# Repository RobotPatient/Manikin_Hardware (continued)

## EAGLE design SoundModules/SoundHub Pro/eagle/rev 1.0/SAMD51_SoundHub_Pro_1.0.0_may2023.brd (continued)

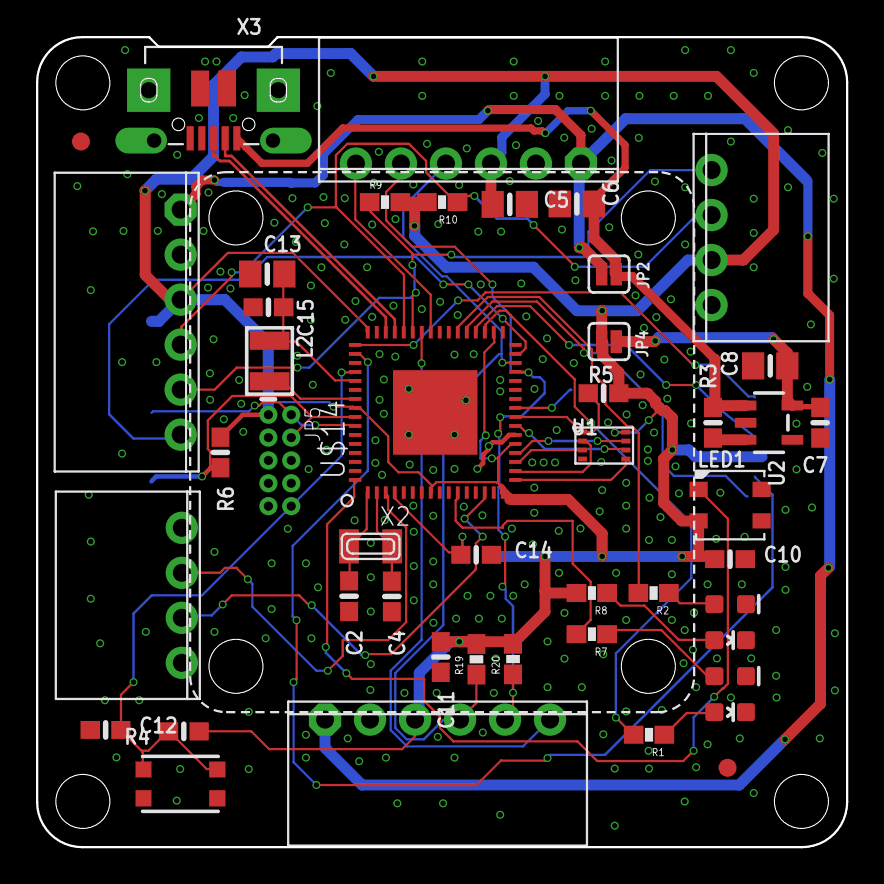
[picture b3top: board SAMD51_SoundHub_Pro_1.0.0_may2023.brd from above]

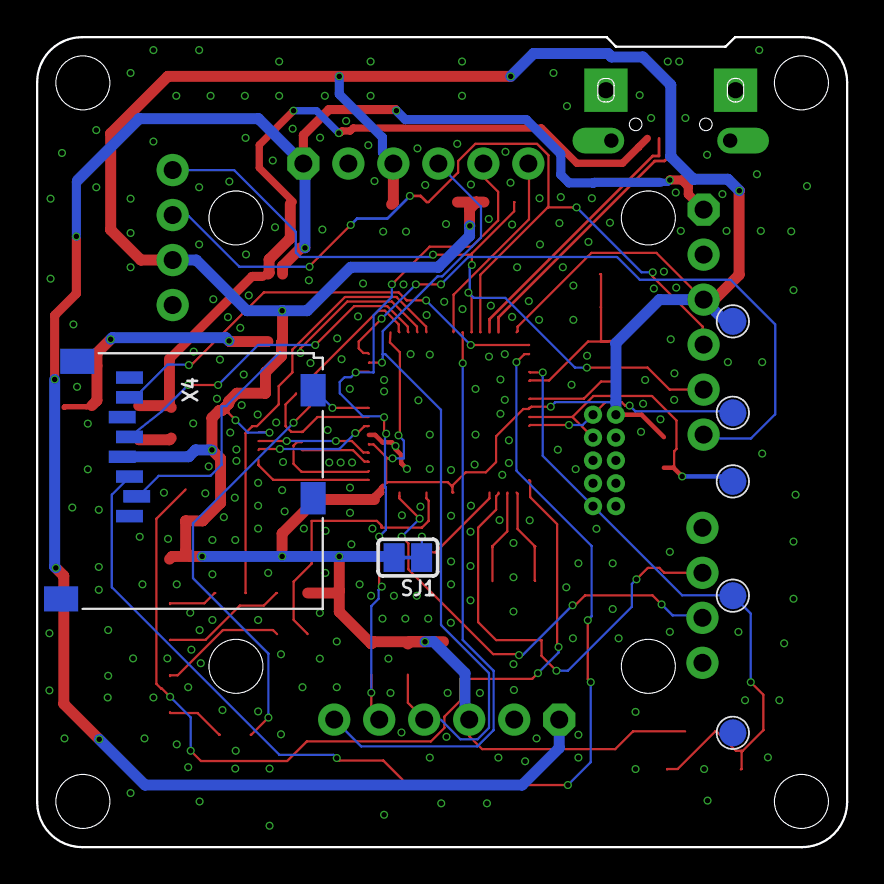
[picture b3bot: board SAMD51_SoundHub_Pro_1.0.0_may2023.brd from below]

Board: 2 copper layers, 45.0 x 45.0 mm, 51 parts (2 on the bottom side), 44 nets.

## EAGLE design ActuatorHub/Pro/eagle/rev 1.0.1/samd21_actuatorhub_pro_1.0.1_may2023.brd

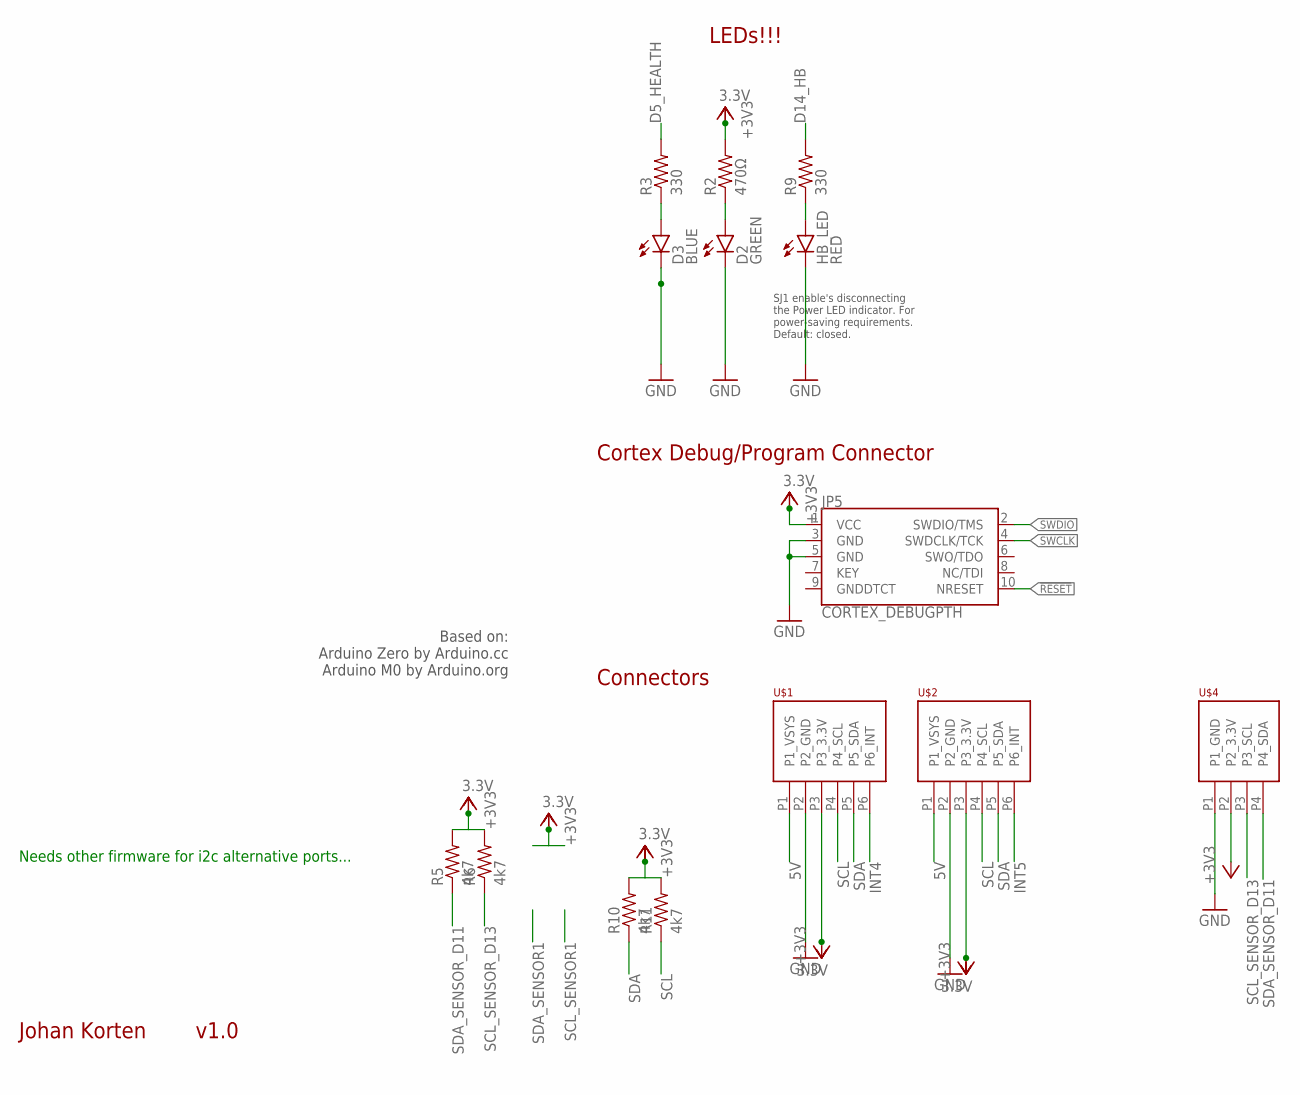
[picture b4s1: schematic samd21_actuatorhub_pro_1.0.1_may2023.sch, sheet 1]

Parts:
D2: GREEN; LED-0603
D3: BLUE; LED-0603
HB_LED: RED; LED-0603
JP5: CORTEX_DEBUGPTH; 2X5-PTH-1.27MM
R2: 470Ω; 0603-RES
R3, R9: 330; 0603-RES
R5, R6, R10, R11: 4k7; 0603-RES
U$1, U$2: PHOENIX_PTSM_M6_TH_I2CPPANGLE; PTSM_M6_THRHOLE
U$4: PHOENIX_PTSM_M4_THANGLE; PTSM_M4_TH

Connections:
3.3V: JP5.1 (VCC), R2.2, R5.2, R6.2, R10.2, R11.2, U$1.P3 (P3_3.3V), U$2.P3 (P3_3.3V), U$4.P2 (P2_3.3V); also elsewhere on the board
5V: U$1.P1 (P1_VSYS), U$2.P1 (P1_VSYS); also elsewhere on the board
!RESET: JP5.10 (NRESET); also elsewhere on the board
D5_HEALTH: R3.2; also elsewhere on the board
D5_HEALTH_LED: D3.A, R3.1
D14_HB: R9.2; also elsewhere on the board
D14_HB_LED: HB_LED.A, R9.1
GND: D2.C, D3.C, HB_LED.C, JP5.3 (GND), JP5.5 (GND), U$1.P2 (P2_GND), U$2.P2 (P2_GND), U$4.P1 (P1_GND); also elsewhere on the board
INT4: U$1.P6 (P6_INT); also elsewhere on the board
INT5: U$2.P6 (P6_INT); also elsewhere on the board
unnamed: D2.A, R2.1
SCL: R11.1, U$1.P4 (P4_SCL), U$2.P4 (P4_SCL); also elsewhere on the board
SCL_SENSOR_D13: R6.1, U$4.P3 (P3_SCL); also elsewhere on the board
SDA: R10.1, U$1.P5 (P5_SDA), U$2.P5 (P5_SDA); also elsewhere on the board
SDA_SENSOR_D11: R5.1, U$4.P4 (P4_SDA); also elsewhere on the board
SWCLK: JP5.4 (SWDCLK/TCK); also elsewhere on the board
SWDIO: JP5.2 (SWDIO/TMS); also elsewhere on the board

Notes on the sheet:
LEDs!!!
Cortex Debug/Program Connector
Connectors
Johan Korten
v1.0
SJ1 enable's disconnecting the Power LED indicator. For power-saving requirements. Default: closed.
Based on: Arduino Zero by Arduino.cc Arduino M0 by Arduino.org
Needs other firmware for i2c alternative ports...

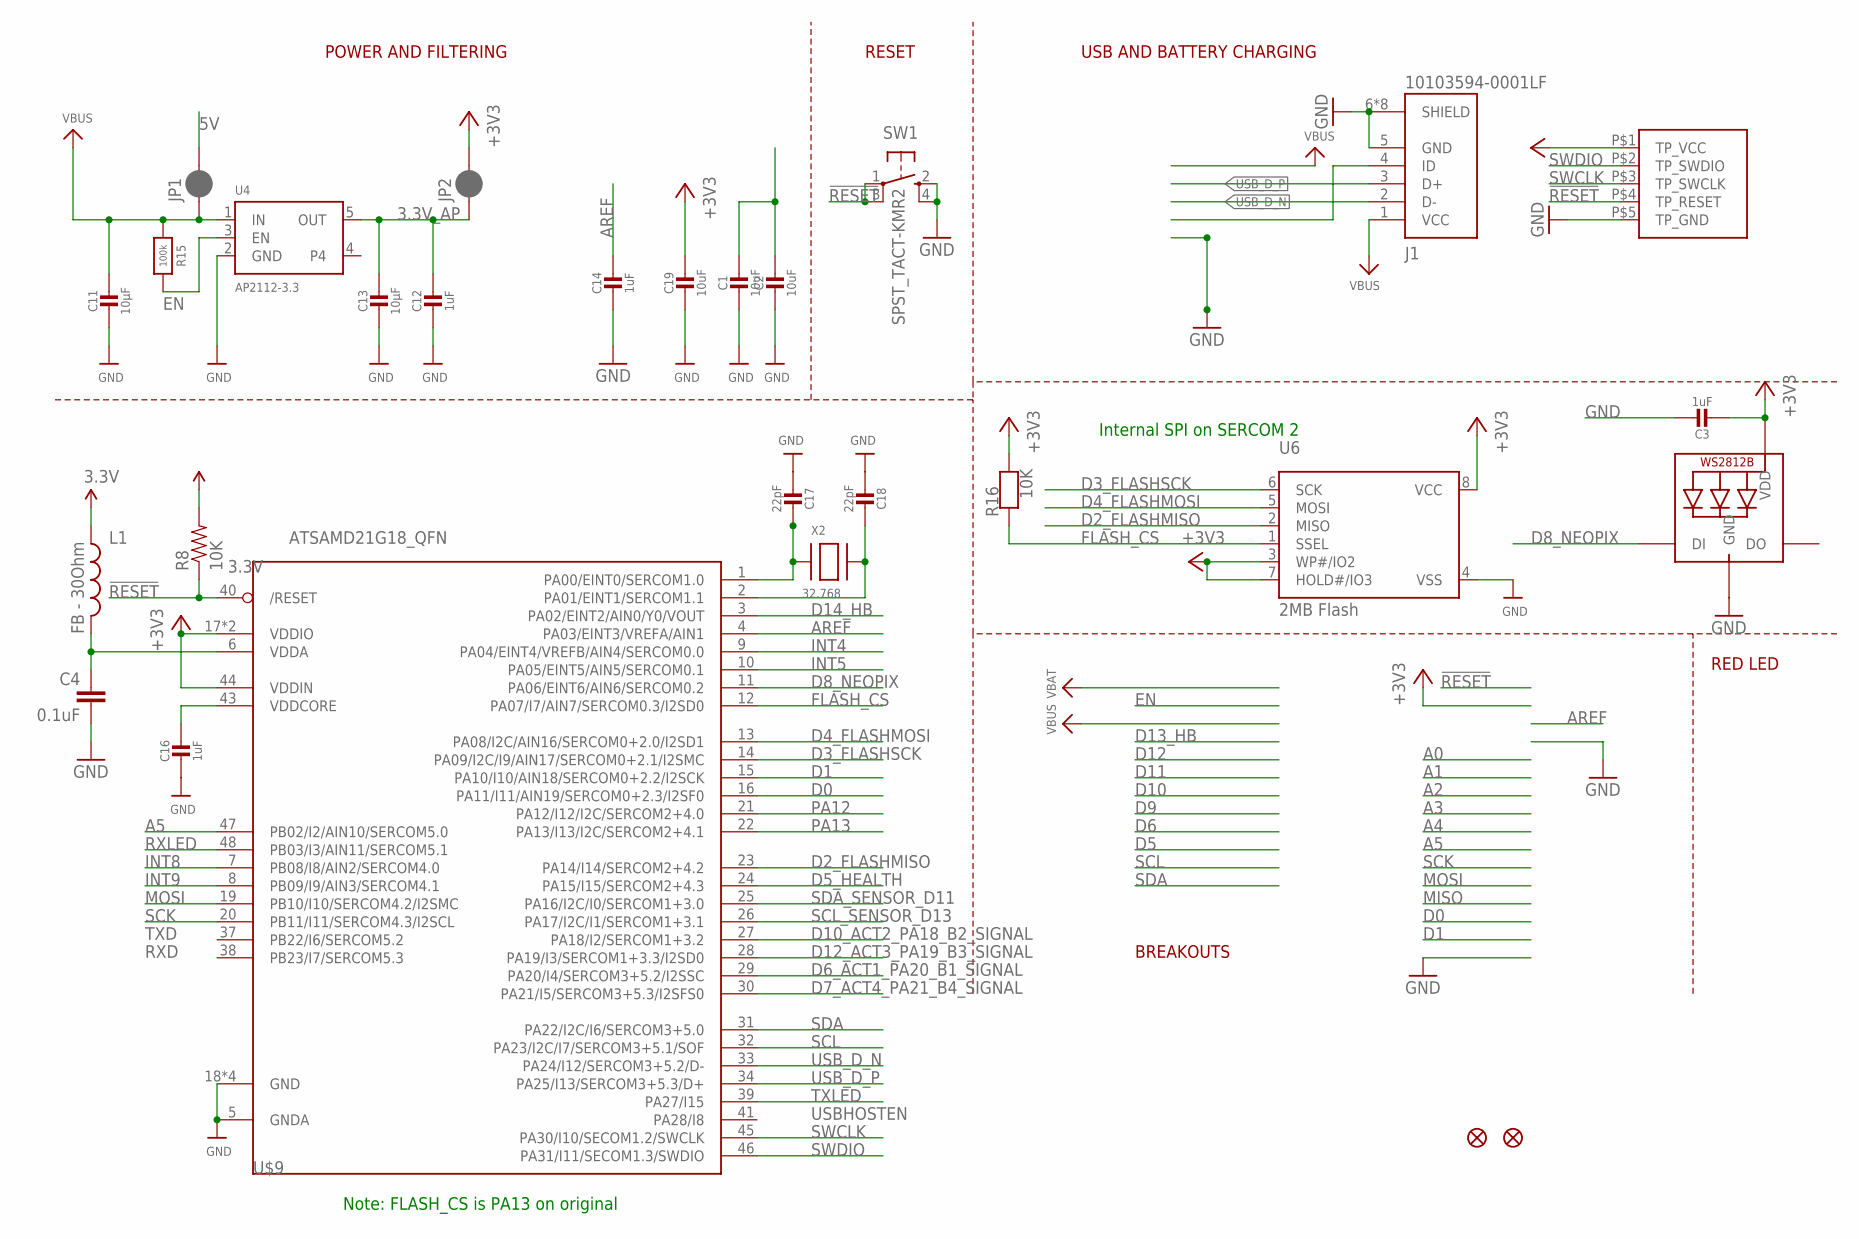
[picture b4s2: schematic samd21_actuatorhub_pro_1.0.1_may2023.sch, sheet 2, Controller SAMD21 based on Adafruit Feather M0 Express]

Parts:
C1, C2, C19: 10uF; 0805-NO
C3, C12, C14, C16: 1uF; 0603-NO
C4: 0.1uF; 0402-CAP
C11, C13: 10µF; 0805-NO
C17, C18: 22pF; 0603-NO
J1: 10103594-0001LF; AMPHENOL_10103594-0001LF
JP1, JP2: JUMPER-SMT_2_NC_PASTE_SILK; SMT-JUMPER_2_NC_PASTE_SILK
L1: FB - 30Ohm; 0603
LED1: WS2812B3535; LED3535
R8: 10K; 0603-RES
R15: 100k; 0603-NO
R16: 10K; 0603-NO
SW1: SPST_TACT-KMR2; KMR2
U4: AP2112-3.3; SOT23-5
U6: 2MB Flash; SOIC8_208MIL
U$5: HUB_TESTPINSHUBS; TEST_PINS
U$9: ATSAMD21G18_QFN; TQFN48_7MM
U$34, U$35: FIDUCIAL""; FIDUCIAL_1MM
X2: 32.768; XTAL3215

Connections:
3.3V: C3.2, C19.1, JP2.2, L1.1, LED1.2 (VDD), R8.2, R16.2, U6.3 (WP#/IO2), U6.7 (HOLD#/IO3), U6.8 (VCC), U$5.P$1 (TP_VCC), U$9.17 (VDDIO), U$9.36 (VDDIO), U$9.44 (VDDIN); also elsewhere on the board
3.3V_AP: C12.1, C13.1, JP2.1, U4.5 (OUT)
5V: C1.1, C2.1, JP1.2; also elsewhere on the board
!RESET: R8.1, SW1.1, SW1.3 (P1), U$5.P$4 (TP_RESET), U$9.40 (/RESET); also elsewhere on the board
A5: U$9.47 (PB02/I2/AIN10/SERCOM5.0)
AREF: C14.1, U$9.4 (PA03/EINT3/VREFA/AIN1)
D0: U$9.16 (PA11/I11/AIN19/SERCOM0+2.3/I2SF0)
D1: U$9.15 (PA10/I10/AIN18/SERCOM0+2.2/I2SCK)
D2_FLASHMISO: U6.2 (MISO), U$9.23 (PA14/I14/SERCOM2+4.2)
D3_FLASHSCK: U6.6 (SCK), U$9.14 (PA09/I2C/I9/AIN17/SERCOM0+2.1/I2SMC)
D4_FLASHMOSI: U6.5 (MOSI), U$9.13 (PA08/I2C/AIN16/SERCOM0+2.0/I2SD1)
D5_HEALTH: U$9.24 (PA15/I15/SERCOM2+4.3); also elsewhere on the board
D6_ACT1_PA20_B1_SIGNAL: U$9.29 (PA20/I4/SERCOM3+5.2/I2SSC); also elsewhere on the board
D7_ACT4_PA21_B4_SIGNAL: U$9.30 (PA21/I5/SERCOM3+5.3/I2SFS0); also elsewhere on the board
D8_NEOPIX: LED1.1 (DI), U$9.11 (PA06/EINT6/AIN6/SERCOM0.2)
D10_ACT2_PA18_B2_SIGNAL: U$9.27 (PA18/I2/SERCOM1+3.2); also elsewhere on the board
D12_ACT3_PA19_B3_SIGNAL: U$9.28 (PA19/I3/SERCOM1+3.3/I2SD0); also elsewhere on the board
D14_HB: U$9.3 (PA02/EINT2/AIN0/Y0/VOUT); also elsewhere on the board
EN: R15.2, U4.3 (EN)
FLASH_CS: R16.1, U6.1 (SSEL), U$9.12 (PA07/I7/AIN7/SERCOM0.3/I2SD0)
GND: C1.2, C2.2, C3.1, C4.2, C11.2, C12.2, C13.2, C14.2, C16.2, C17.2, C18.2, C19.2, J1.5 (GND), J1.6 (SHIELD), J1.7 (SHIELD), J1.8 (SHIELD), J1.9 (SHIELD), J1.10 (SHIELD), J1.11 (SHIELD), J1.S1 (SHIELD), J1.S2 (SHIELD), LED1.4 (GND), SW1.2 (S), SW1.4 (S1), U4.2 (GND), U6.4 (VSS), U$5.P$5 (TP_GND), U$9.5 (GNDA), U$9.18 (GND), U$9.35 (GND), U$9.42 (GND), U$9.THERMAL (GND); also elsewhere on the board
INT4: U$9.9 (PA04/EINT4/VREFB/AIN4/SERCOM0.0); also elsewhere on the board
INT5: U$9.10 (PA05/EINT5/AIN5/SERCOM0.1); also elsewhere on the board
INT8: U$9.7 (PB08/I8/AIN2/SERCOM4.0)
INT9: U$9.8 (PB09/I9/AIN3/SERCOM4.1)
MOSI: U$9.19 (PB10/I10/SERCOM4.2/I2SMC)
unnamed: C17.1, U$9.1 (PA00/EINT0/SERCOM1.0), X2.P$1
unnamed: C18.1, U$9.2 (PA01/EINT1/SERCOM1.1), X2.P$2
PA12: U$9.21 (PA12/I12/I2C/SERCOM2+4.0)
PA13: U$9.22 (PA13/I13/I2C/SERCOM2+4.1)
RXLED: U$9.48 (PB03/I3/AIN11/SERCOM5.1)
SCK: U$9.20 (PB11/I11/SERCOM4.3/I2SCL)
SCL: U$9.32 (PA23/I2C/I7/SERCOM3+5.1/SOF); also elsewhere on the board
SCL_SENSOR_D13: U$9.26 (PA17/I2C/I1/SERCOM1+3.1); also elsewhere on the board
SDA: U$9.31 (PA22/I2C/I6/SERCOM3+5.0); also elsewhere on the board
SDA_SENSOR_D11: U$9.25 (PA16/I2C/I0/SERCOM1+3.0); also elsewhere on the board
SWCLK: U$5.P$3 (TP_SWCLK), U$9.45 (PA30/I10/SECOM1.2/SWCLK); also elsewhere on the board
SWDIO: U$5.P$2 (TP_SWDIO), U$9.46 (PA31/I11/SECOM1.3/SWDIO); also elsewhere on the board
TXLED: U$9.39 (PA27/I15)
USB_D_N: J1.2 (D-), U$9.33 (PA24/I12/SERCOM3+5.2/D-)
USB_D_P: J1.3 (D+), U$9.34 (PA25/I13/SERCOM3+5.3/D+)
VBUS: C11.1, J1.1 (VCC), JP1.1, R15.1, U4.1 (IN)
VDDANA: C4.1, L1.2, U$9.6 (VDDA)
VDDCORE1: C16.1, U$9.43 (VDDCORE)

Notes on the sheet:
POWER AND FILTERING
RESET
USBHOSTEN
TXD
RXD
USB AND BATTERY CHARGING
BREAKOUTS
RED LED
Internal SPI on SERCOM 2
Note: FLASH_CS is PA13 on original

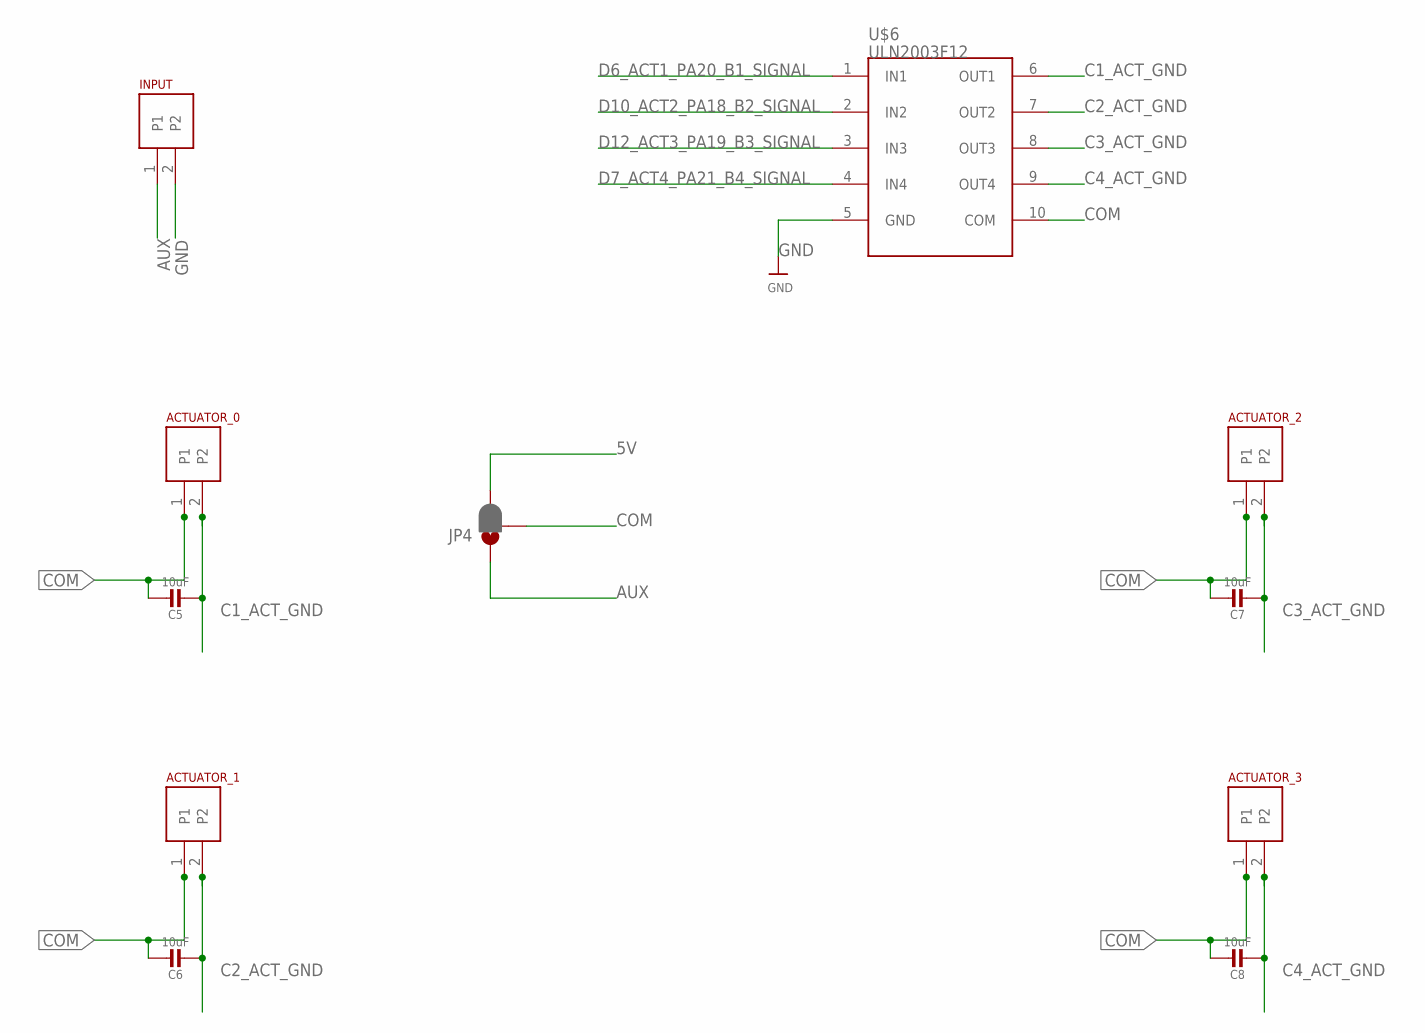
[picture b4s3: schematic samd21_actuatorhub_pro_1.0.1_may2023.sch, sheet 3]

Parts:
ACTUATOR_0, ACTUATOR_1: PHOENIX_PTSM_M2_TH; PTSM_M2_THRHOLE
ACTUATOR_2, ACTUATOR_3: PHOENIX_PTSM_M2TH; PTSM_M2_THRHOLE
C5, C6, C7, C8: 10uF; 0805-NO
INPUT: PHOENIX_PTSM_M2_TH; PTSM_M2_THRHOLE
JP4: JUMPER-SMT_3_1-NC_PASTE_SILK; SMT-JUMPER_3_1-NC_PASTE_SILK
U$6: ULN2003F12; U-DFN3030-10

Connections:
5V: JP4.3; also elsewhere on the board
AUX: INPUT.1, JP4.1
C1_ACT_GND: ACTUATOR_0.2, C5.2, U$6.6 (OUT1)
C2_ACT_GND: ACTUATOR_1.2, C6.2, U$6.7 (OUT2)
C3_ACT_GND: ACTUATOR_2.2, C7.2, U$6.8 (OUT3)
C4_ACT_GND: ACTUATOR_3.2, C8.2, U$6.9 (OUT4)
COM: ACTUATOR_0.1, ACTUATOR_1.1, ACTUATOR_2.1, ACTUATOR_3.1, C5.1, C6.1, C7.1, C8.1, JP4.2, U$6.10 (COM)
D6_ACT1_PA20_B1_SIGNAL: U$6.1 (IN1); also elsewhere on the board
D7_ACT4_PA21_B4_SIGNAL: U$6.4 (IN4); also elsewhere on the board
D10_ACT2_PA18_B2_SIGNAL: U$6.2 (IN2); also elsewhere on the board
D12_ACT3_PA19_B3_SIGNAL: U$6.3 (IN3); also elsewhere on the board
GND: INPUT.2, U$6.5 (GND); also elsewhere on the board

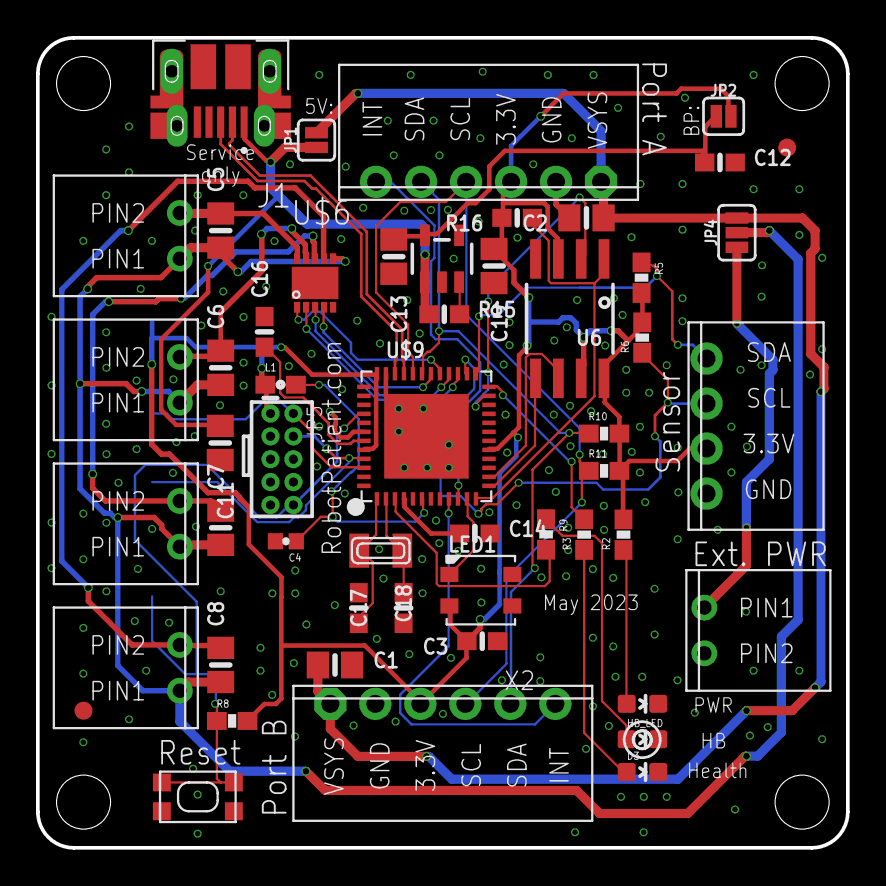
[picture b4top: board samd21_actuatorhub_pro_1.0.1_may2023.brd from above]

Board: 2 copper layers, 45.0 x 45.0 mm, 53 parts (0 on the bottom side), 42 nets.

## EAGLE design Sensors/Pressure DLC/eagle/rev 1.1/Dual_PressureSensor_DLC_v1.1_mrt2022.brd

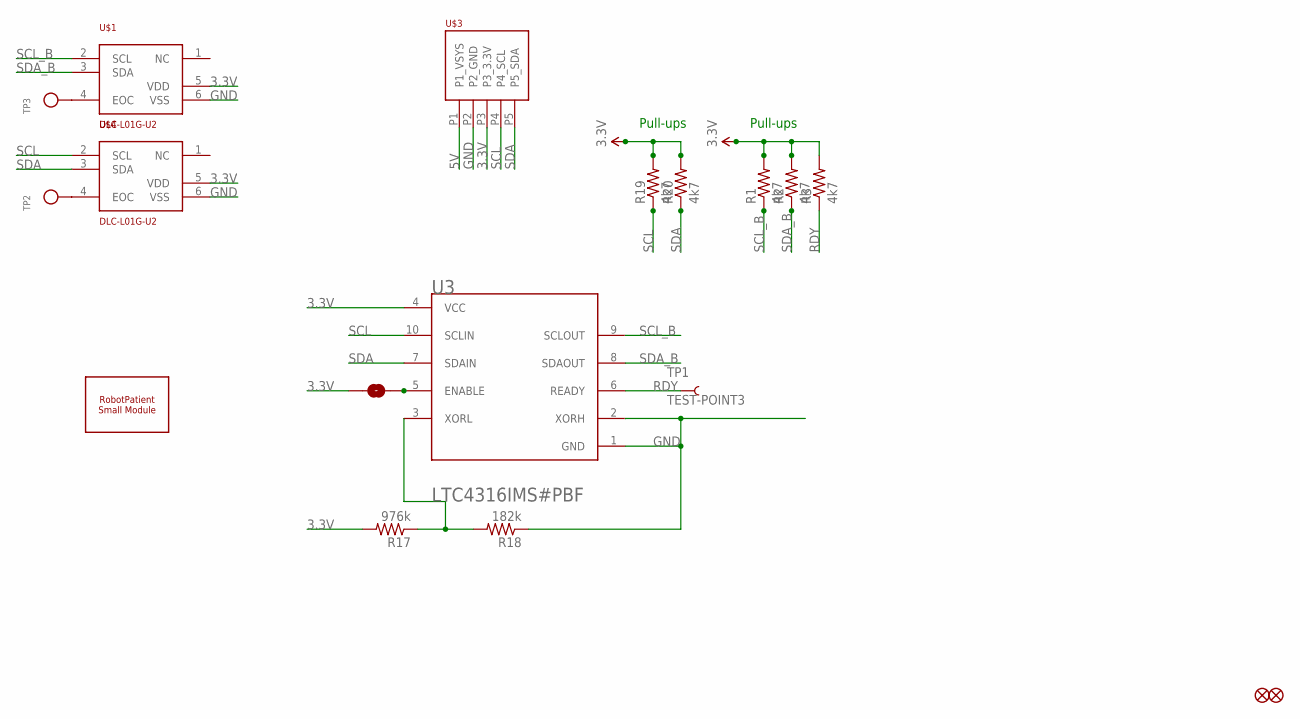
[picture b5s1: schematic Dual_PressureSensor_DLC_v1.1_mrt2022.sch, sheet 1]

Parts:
FID1, FID2: FIDUCIAL""; FIDUCIAL_1MM
JP3: JUMPER-SMT_2_NO_NO-SILK; SMT-JUMPER_2_NO_NO-SILK
R1, R2, R3, R19, R20: 4k7; 0603-RES
R17: 976k; 0603-RES
R18: 182k; 0603-RES
TP1: TEST-POINT3; PAD.03X.03
TP2, TP3: TESTPOINTROUND1MM; TESTPOINT_ROUND_1MM
U3: ANALOG_DEVICES_LTC4316IMS#PBFANALOG_DEVICES_LTC43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; ANALOG_DEVICES_LTC4316IMS#PBF_0
U$1, U$4: DLC-L01G-U2
U$2: ROBOTPATIENT_SMALL_MODULEBOARD; RP_SMALL_SENSOR_OUTLINE
U$3: PHOENIX_PTSM_M5_TH_I2C++; PTSM_M5_THRHOLE

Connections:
3.3V: JP3.1, R1.2, R2.2, R3.2, R17.2, R19.2, R20.2, U3.4 (VCC), U$1.5 (VDD), U$3.P3 (P3_3.3V), U$4.5 (VDD); also elsewhere on the board
5V: U$3.P1 (P1_VSYS); also elsewhere on the board
GND: R18.1, U3.1 (GND), U3.2 (XORH), U$1.6 (VSS), U$3.P2 (P2_GND), U$4.6 (VSS); also elsewhere on the board
unnamed: TP2.P$1, U$4.4 (EOC)
unnamed: TP3.P$1, U$1.4 (EOC)
unnamed: JP3.2, U3.5 (ENABLE)
unnamed: R17.1, R18.2, U3.3 (XORL)
RDY: R3.1, TP1.P$1, U3.6 (READY)
SCL: R19.1, U3.10 (SCLIN), U$3.P4 (P4_SCL), U$4.2 (SCL)
SCL_B: R1.1, U3.9 (SCLOUT), U$1.2 (SCL)
SDA: R20.1, U3.7 (SDAIN), U$3.P5 (P5_SDA), U$4.3 (SDA)
SDA_B: R2.1, U3.8 (SDAOUT), U$1.3 (SDA)

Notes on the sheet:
Pull-ups

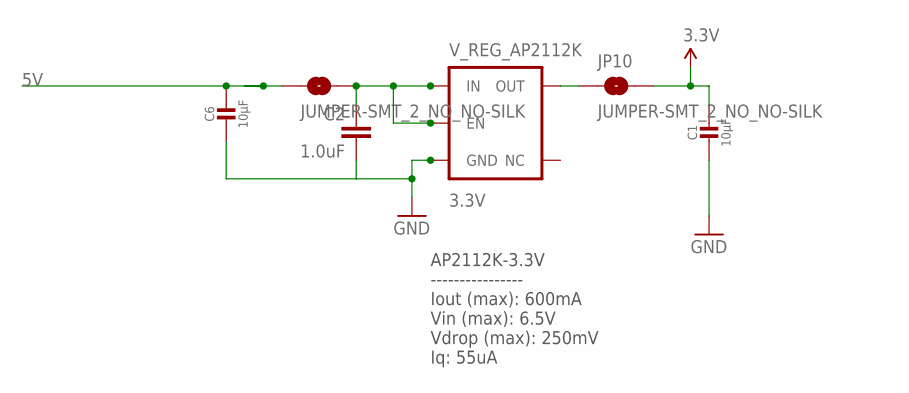
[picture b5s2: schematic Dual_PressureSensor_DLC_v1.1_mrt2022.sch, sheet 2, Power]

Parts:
C1, C6: 10µF; 0805-NO
C2: 1.0uF; 0805-CAP
JP10, JP11: JUMPER-SMT_2_NO_NO-SILK; SMT-JUMPER_2_NO_NO-SILK
V_REG_AP2112K: 3.3V; SOT23-5

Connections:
3.3V: C1.1, JP10.2; also elsewhere on the board
5V: C6.1, JP11.1; also elsewhere on the board
GND: C1.2, C2.2, C6.2, V_REG_AP2112K.2 (GND); also elsewhere on the board
unnamed: JP10.1, V_REG_AP2112K.5 (OUT)
unnamed: C2.1, JP11.2, V_REG_AP2112K.1 (IN), V_REG_AP2112K.3 (EN)

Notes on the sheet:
AP2112K-3.3V ---------------- Iout (max): 600mA Vin (max): 6.5V Vdrop (max): 250mV Iq: 55uA

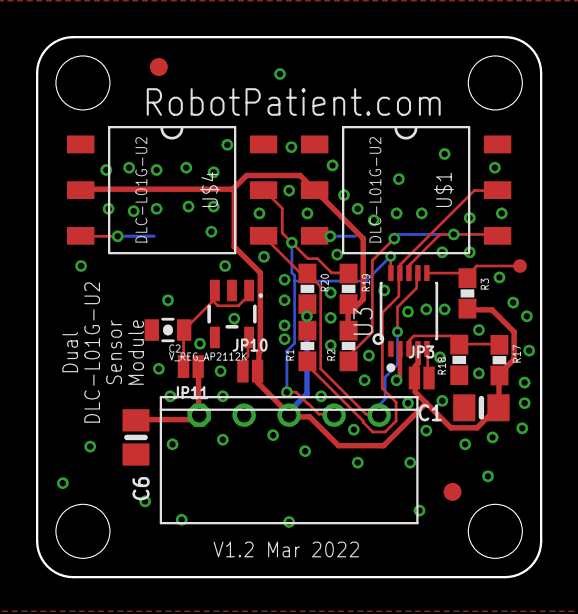
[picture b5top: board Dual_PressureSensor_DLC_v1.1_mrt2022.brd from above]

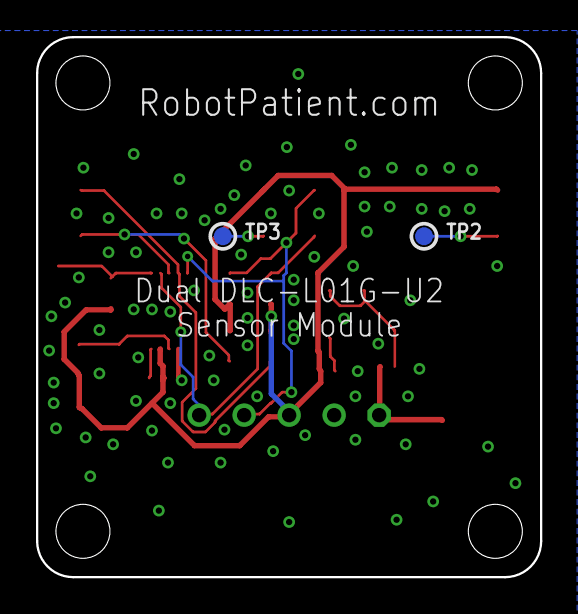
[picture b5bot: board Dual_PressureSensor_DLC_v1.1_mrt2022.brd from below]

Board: 2 copper layers, 28.0 x 30.0 mm, 24 parts (2 on the bottom side), 14 nets.

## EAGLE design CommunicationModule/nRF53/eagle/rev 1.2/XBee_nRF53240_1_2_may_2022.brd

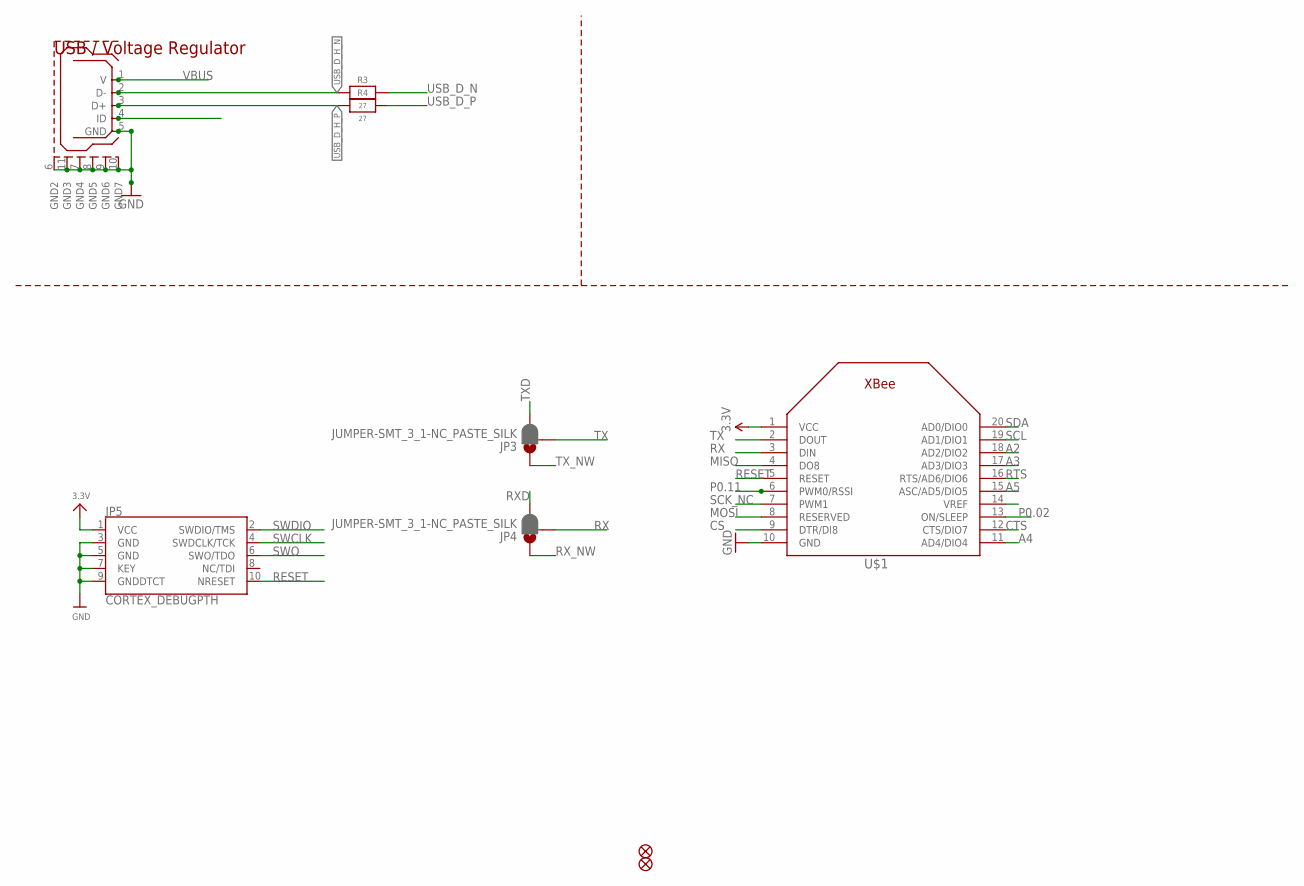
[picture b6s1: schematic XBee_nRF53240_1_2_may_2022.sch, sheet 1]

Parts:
FID1, FID3: FIDUCIAL_1MM
JP3, JP4: JUMPER-SMT_3_1-NC_PASTE_SILK; SMT-JUMPER_3_1-NC_PASTE_SILK
JP5: CORTEX_DEBUGPTH; 2X5-PTH-1.27MM
R3, R4: 27; 0603-NO
U$1: XBEE
U$2: USB_MICROB; USB_MICROB_PACKAGE

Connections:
3.3V: JP5.1 (VCC), U$1.1 (VCC); also elsewhere on the board
A2: U$1.18 (AD2/DIO2)
A3: U$1.17 (AD3/DIO3)
A4: U$1.11 (AD4/DIO4)
A5: U$1.15 (ASC/AD5/DIO5)
CS: U$1.9 (DTR/DI8)
CTS: U$1.12 (CTS/DIO7); also elsewhere on the board
GND: JP5.3 (GND), JP5.5 (GND), JP5.7 (KEY), JP5.9 (GNDDTCT), U$1.10 (GND), U$2.5 (GND), U$2.6 (GND2), U$2.7 (GND4), U$2.8 (GND5), U$2.9 (GND6), U$2.10 (GND7), U$2.11 (GND3); also elsewhere on the board
MISO: U$1.4 (DO8)
MOSI: U$1.8 (RESERVED)
P0.02: U$1.13 (ON/SLEEP)
P0.11: U$1.6 (PWM0/RSSI)
RESET: JP5.10 (NRESET), U$1.5 (RESET); also elsewhere on the board
RTS: U$1.16 (RTS/AD6/DIO6); also elsewhere on the board
RX: JP4.2, U$1.3 (DIN)
RXD: JP4.3; also elsewhere on the board
RX_NW: JP4.1; also elsewhere on the board
SCK_NC: U$1.7 (PWM1)
SCL: U$1.19 (AD1/DIO1); also elsewhere on the board
SDA: U$1.20 (AD0/DIO0); also elsewhere on the board
SWCLK: JP5.4 (SWDCLK/TCK); also elsewhere on the board
SWDIO: JP5.2 (SWDIO/TMS); also elsewhere on the board
SWO: JP5.6 (SWO/TDO)
TX: JP3.2, U$1.2 (DOUT)
TXD: JP3.3; also elsewhere on the board
TX_NW: JP3.1; also elsewhere on the board
USB_D_H_N: R3.1, U$2.2 (D-)
USB_D_H_P: R4.1, U$2.3 (D+)
USB_D_N: R3.2; also elsewhere on the board
USB_D_P: R4.2; also elsewhere on the board
VBUS: U$2.1 (V); also elsewhere on the board

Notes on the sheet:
USB / Voltage Regulator

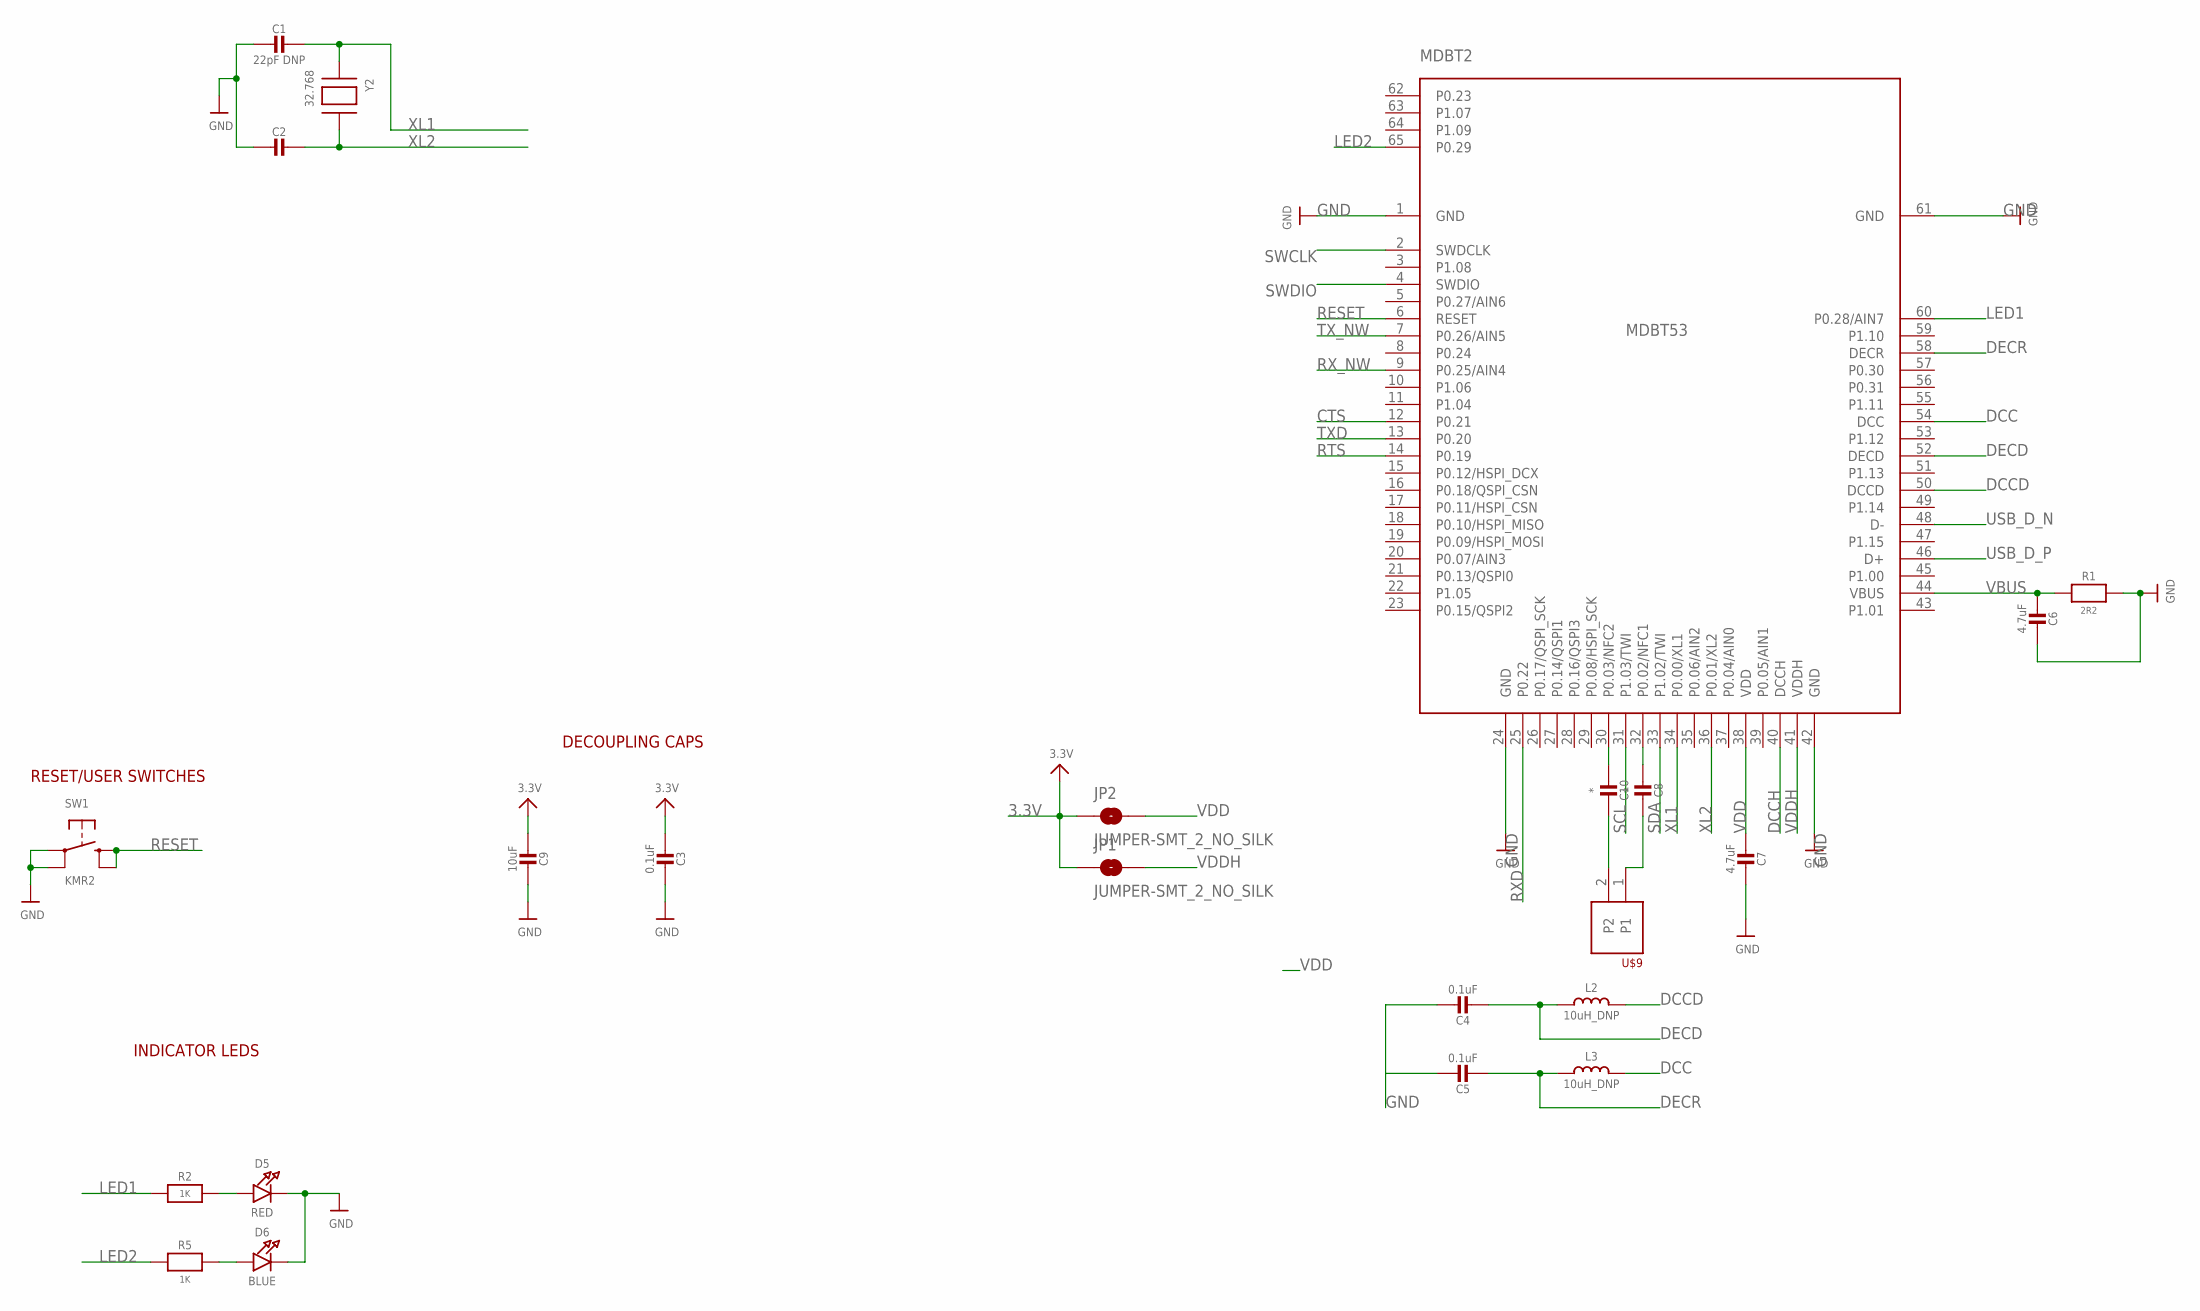
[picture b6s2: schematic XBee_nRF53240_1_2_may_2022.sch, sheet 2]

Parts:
C1, C2: 22pF DNP; 0603-NO
C3, C4, C5: 0.1uF; 0603-NO
C6, C7: 4.7uF; 0805-NO
C8, C10: *; 0603-NO
C9: 10uF; 0805-NO
D5: RED; CHIPLED_0805_NOOUTLINE
D6: BLUE; CHIPLED_0805_NOOUTLINE
JP1, JP2: JUMPER-SMT_2_NO_SILK; SMT-JUMPER_2_NO_SILK
L2, L3: 10uH_DNP; _0805MP
MDBT2: MDBT53
R1: 2R2; 0603-NO
R2, R5: 1K; 0603-NO
SW1: KMR2; BTN_KMR2_4.6X2.8
U$9: PHOENIX_PTSM_M2_TH; PTSM_M2_THRHOLE
Y2: 32.768; XTAL3215

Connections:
3.3V: C3.2, C9.2, JP1.1, JP2.1; also elsewhere on the board
CTS: MDBT2.12 (P0.21); also elsewhere on the board
DCC: L3.2, MDBT2.54 (DCC)
DCCD: L2.2, MDBT2.50 (DCCD)
DCCH: MDBT2.40 (DCCH)
DECD: C4.2, L2.1, MDBT2.52 (DECD)
DECR: C5.2, L3.1, MDBT2.58 (DECR)
GND: C1.2, C2.2, C3.1, C4.1, C6.1, C7.1, C9.1, D5.C, D6.C, MDBT2.1 (GND), MDBT2.24 (GND), MDBT2.42 (GND), MDBT2.61 (GND), R1.2, SW1.A, SW1.A' (P1); also elsewhere on the board
LED1: MDBT2.60 (P0.28/AIN7), R2.1
LED2: MDBT2.65 (P0.29), R5.1
unnamed: C10.2, MDBT2.30 (P0.03/NFC2)
unnamed: C8.2, MDBT2.32 (P0.02/NFC1)
unnamed: C10.1, U$9.2
unnamed: C8.1, U$9.1
unnamed: D6.A, R5.2
unnamed: D5.A, R2.2
RESET: MDBT2.6 (RESET), SW1.B (S), SW1.B' (S1); also elsewhere on the board
RTS: MDBT2.14 (P0.19); also elsewhere on the board
RXD: MDBT2.25 (P0.22); also elsewhere on the board
RX_NW: MDBT2.9 (P0.25/AIN4); also elsewhere on the board
SCL: MDBT2.31 (P1.03/TWI); also elsewhere on the board
SDA: MDBT2.33 (P1.02/TWI); also elsewhere on the board
SWCLK: MDBT2.2 (SWDCLK); also elsewhere on the board
SWDIO: MDBT2.4 (SWDIO); also elsewhere on the board
TXD: MDBT2.13 (P0.20); also elsewhere on the board
TX_NW: MDBT2.7 (P0.26/AIN5); also elsewhere on the board
USB_D_N: MDBT2.48 (D-); also elsewhere on the board
USB_D_P: MDBT2.46 (D+); also elsewhere on the board
VBUS: C6.2, MDBT2.44 (VBUS), R1.1; also elsewhere on the board
VDD: C7.2, JP2.2, MDBT2.38 (VDD)
VDDH: JP1.2, MDBT2.41 (VDDH)
XL1: C1.1, MDBT2.34 (P0.00/XL1), Y2.P$1
XL2: C2.1, MDBT2.36 (P0.01/XL2), Y2.P$2

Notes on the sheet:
INDICATOR LEDS
RESET/USER SWITCHES
DECOUPLING CAPS

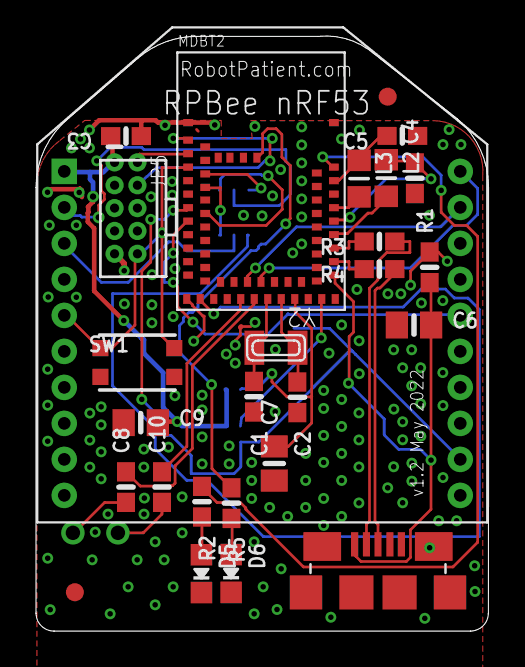
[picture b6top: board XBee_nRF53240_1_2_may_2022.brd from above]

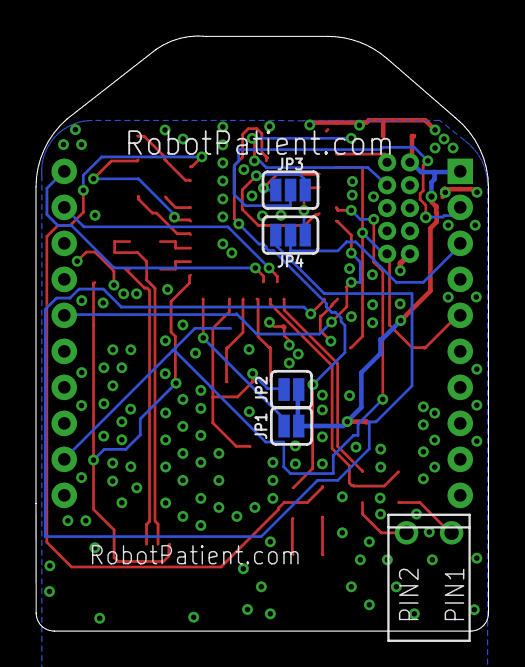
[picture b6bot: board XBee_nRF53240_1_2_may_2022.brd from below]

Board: 2 copper layers, 25.1 x 33.1 mm, 32 parts (5 on the bottom side), 36 nets.
